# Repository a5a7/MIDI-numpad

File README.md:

# MIDI Numpad

(All the files say keyboard because that was the original idea...)

I miscounted the number of keys in a single scale (12) as 11. Thus, this is now a numpad. It has a rotary encoder (something I'm going to use to adjust the pitch) and a potentiometer (which is going to adjust volume). It'll be fun to see how different numbers sound. 

## Final PCB Design

The routing went much better compared to last time. I actually finally understood how to use the bottom layer, which was incredibly helpful to making it better (I also experimented a lot more with the schematic to rearrange things to make things nicer). 

The schematic and PCB are all in this repository. 

## Firmware

Located in the firmware/sketch. It's currently a testing script to play a sound on loop, once I get the physical board I will implement it fully because I have no idea if this will actually work, and I'd prefer to use a physical board to see live what happens with the code.

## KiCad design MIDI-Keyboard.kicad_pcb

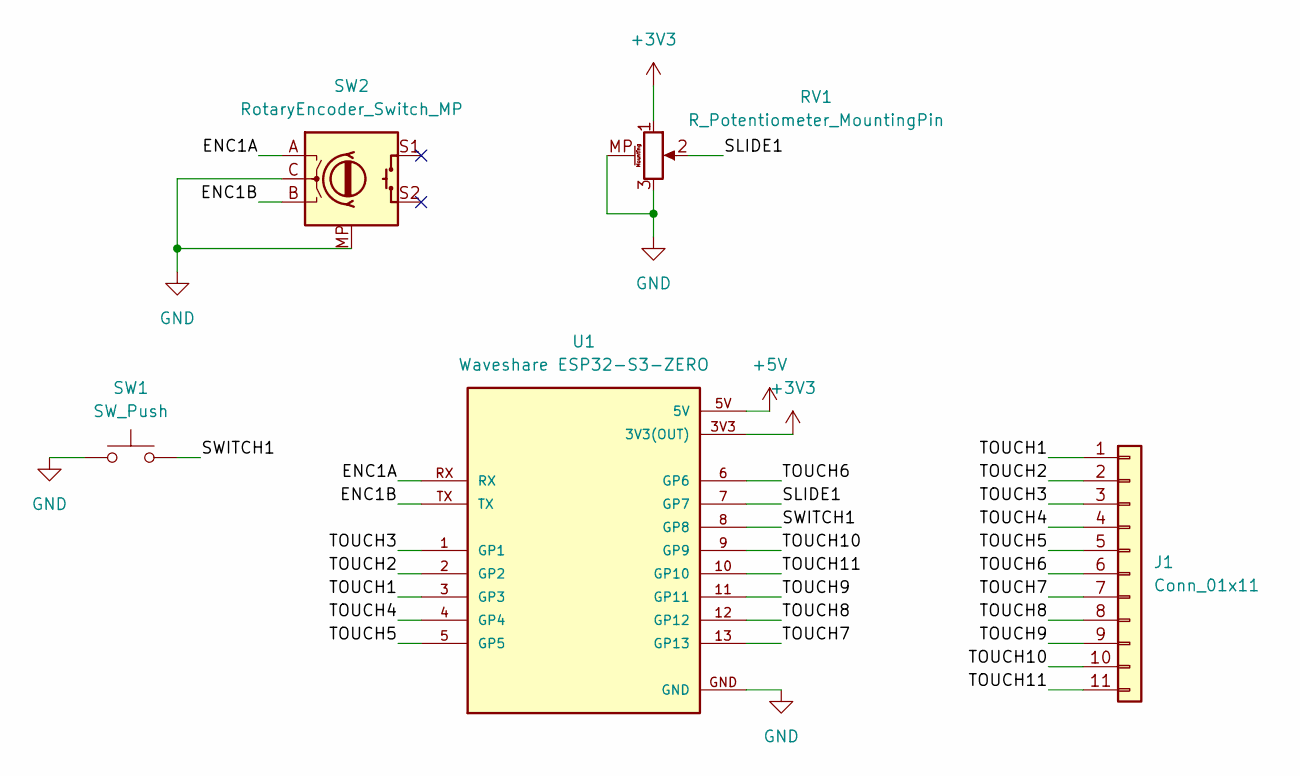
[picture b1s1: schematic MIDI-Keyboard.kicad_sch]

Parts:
J1: Conn_01x11; Library
RV1: R_Potentiometer_MountingPin; Potentiometer_Bourns_PTA1543_Single_Slide
SW1: SW_Push; Kailh Choc Low-Profile Switches
SW2: RotaryEncoder_Switch_MP; RotaryEncoder_Alps_EC11E-Switch_Vertical_H20mm
U1: Waveshare ESP32-S3-ZERO; Waveshare ESP32-S3-Zero; PARTREV NA

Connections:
+3V3: RV1.1, U1.3V3 (3V3(OUT))
+5V: U1.5V
/ENC1A: SW2.A, U1.RX
/ENC1B: SW2.B, U1.TX
/SLIDE1: RV1.2, U1.7 (GP7)
/SWITCH1: SW1.2, U1.8 (GP8)
/TOUCH1: J1.1, U1.3 (GP3)
/TOUCH2: J1.2, U1.2 (GP2)
/TOUCH3: J1.3, U1.1 (GP1)
/TOUCH4: J1.4, U1.4 (GP4)
/TOUCH5: J1.5, U1.5 (GP5)
/TOUCH6: J1.6, U1.6 (GP6)
/TOUCH7: J1.7, U1.13 (GP13)
/TOUCH8: J1.8, U1.12 (GP12)
/TOUCH9: J1.9, U1.11 (GP11)
/TOUCH10: J1.10, U1.9 (GP9)
/TOUCH11: J1.11, U1.10 (GP10)
GND: RV1.3, RV1.MP (MountPin), SW1.1, SW2.C, SW2.MP, U1.GND

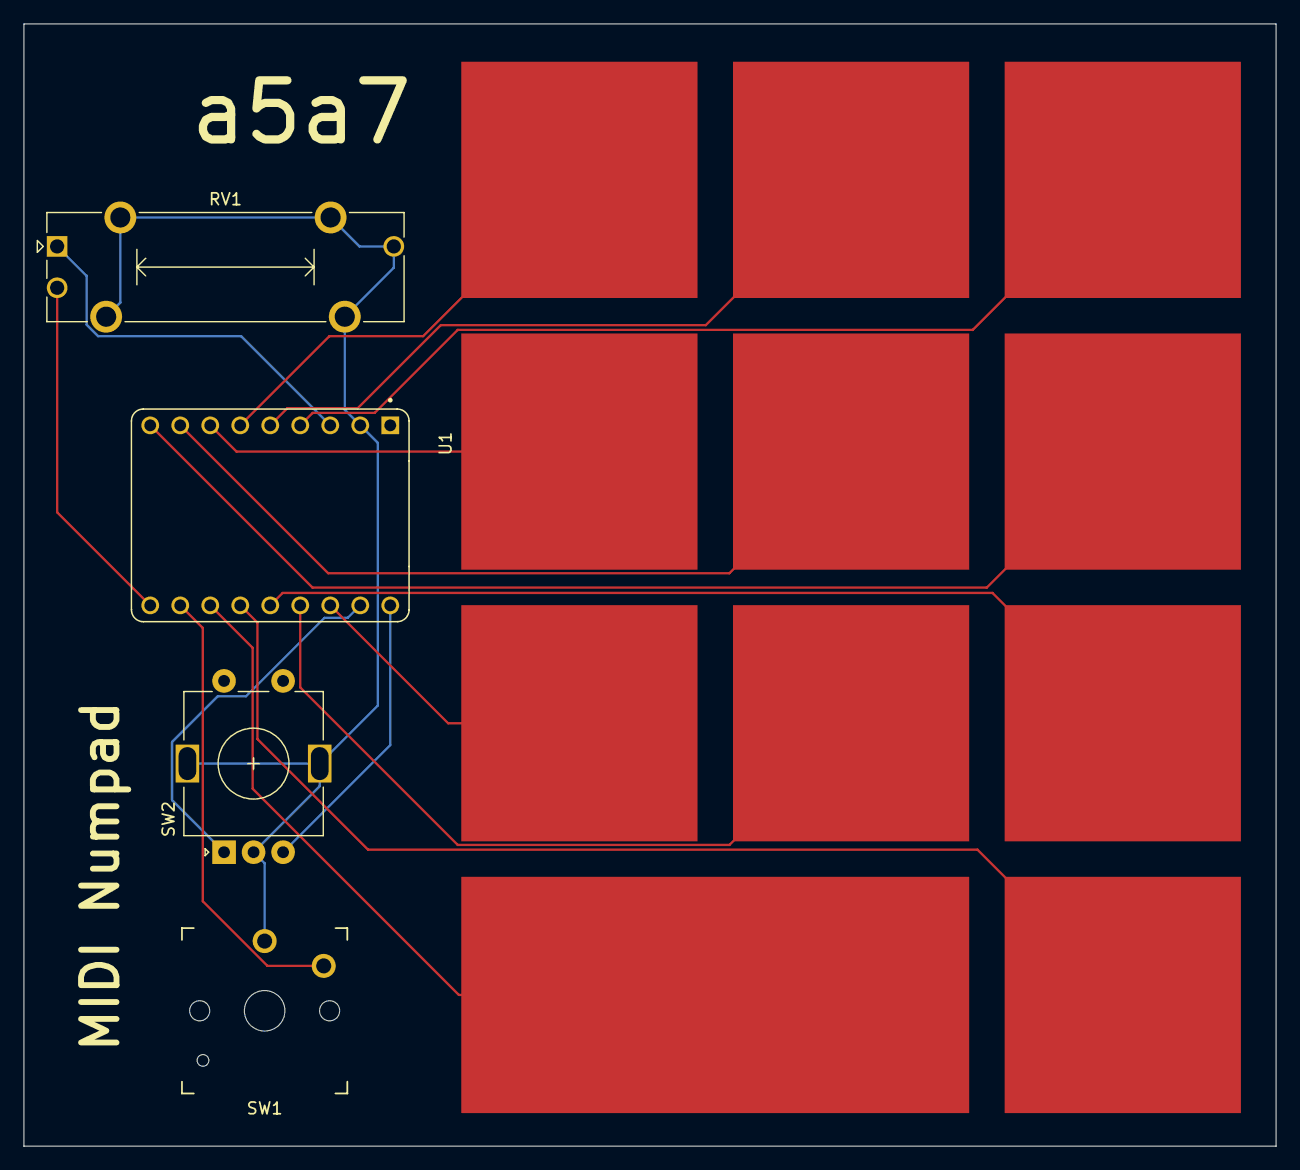
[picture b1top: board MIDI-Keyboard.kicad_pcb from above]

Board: 2 copper layers, 106.0 x 95.0 mm, 5 parts (0 on the bottom side), 17 nets.

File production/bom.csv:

Designator,Footprint,Quantity,Value,LCSC Part #
J1,Library,1,Conn_01x11,
RV1,Potentiometer_Bourns_PTA1543_Single_Slide,1,R_Potentiometer_MountingPin,
SW1,Kailh Choc Low-Profile Switches,1,SW_Push,
SW2,RotaryEncoder_Alps_EC11E-Switch_Vertical_H20mm,1,RotaryEncoder_Switch_MP,
U1,Waveshare ESP32-S3-Zero,1,Waveshare ESP32-S3-ZERO,
